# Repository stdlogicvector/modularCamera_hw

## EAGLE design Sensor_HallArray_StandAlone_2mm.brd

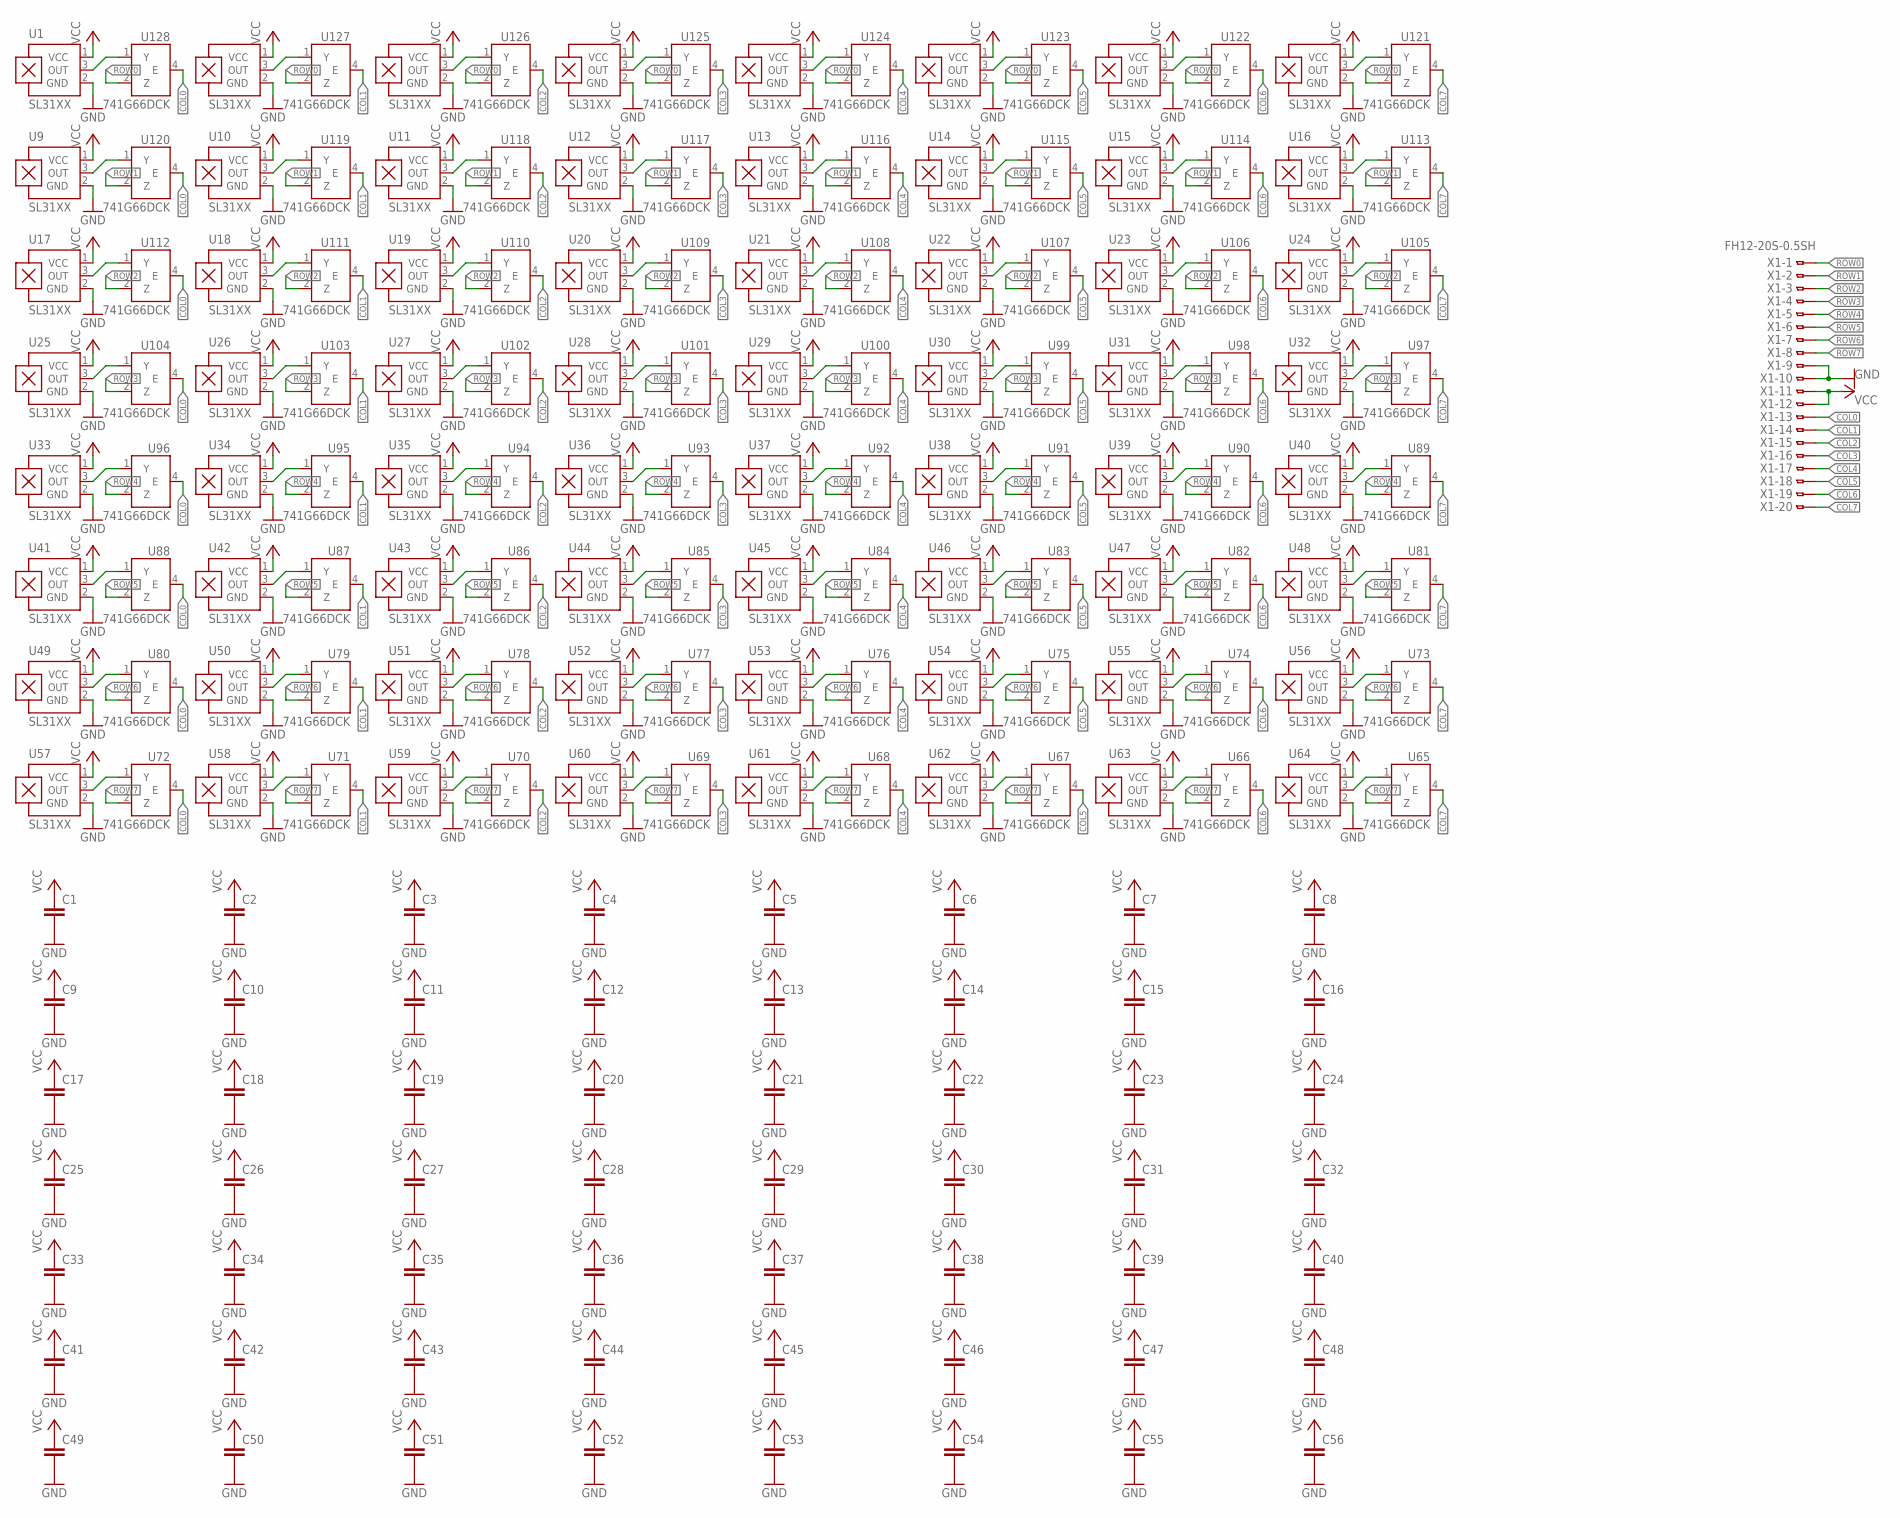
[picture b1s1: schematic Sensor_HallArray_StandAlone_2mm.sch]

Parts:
C1, C2, C3, C4, C5, C6, C7, C8, C9, C10, C11, C12, C13, C14, C15, C16, C17, C18, C19, C20, C21, C22, C23, C24, C25, C26, C27, C28, C29, C30, C31, C32, C33, C34, C35, C36, C37, C38, C39, C40, C41, C42, C43, C44, C45, C46, C47, C48, C49, C50, C51, C52, C53, C54, C55, C56: C-EUC0201; C0201
U1, U2, U3, U4, U5, U6, U7, U8, U9, U10, U11, U12, U13, U14, U15, U16, U17, U18, U19, U20, U21, U22, U23, U24, U25, U26, U27, U28, U29, U30, U31, U32, U33, U34, U35, U36, U37, U38, U39, U40, U41, U42, U43, U44, U45, U46, U47, U48, U49, U50, U51, U52, U53, U54, U55, U56, U57, U58, U59, U60, U61, U62, U63, U64: SL31XX; SOT1215
U65, U66, U67, U68, U69, U70, U71, U72, U73, U74, U75, U76, U77, U78, U79, U80, U81, U82, U83, U84, U85, U86, U87, U88, U89, U90, U91, U92, U93, U94, U95, U96, U97, U98, U99, U100, U101, U102, U103, U104, U105, U106, U107, U108, U109, U110, U111, U112, U113, U114, U115, U116, U117, U118, U119, U120, U121, U122, U123, U124, U125, U126, U127, U128: 741G66DCK; SC70-5
X1: FH12-20S-0.5SH

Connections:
COL0: U72.4 (E), U80.4 (E), U88.4 (E), U96.4 (E), U104.4 (E), U112.4 (E), U120.4 (E), U128.4 (E), X1.13
COL1: U71.4 (E), U79.4 (E), U87.4 (E), U95.4 (E), U103.4 (E), U111.4 (E), U119.4 (E), U127.4 (E), X1.14
COL2: U70.4 (E), U78.4 (E), U86.4 (E), U94.4 (E), U102.4 (E), U110.4 (E), U118.4 (E), U126.4 (E), X1.15
COL3: U69.4 (E), U77.4 (E), U85.4 (E), U93.4 (E), U101.4 (E), U109.4 (E), U117.4 (E), U125.4 (E), X1.16
COL4: U68.4 (E), U76.4 (E), U84.4 (E), U92.4 (E), U100.4 (E), U108.4 (E), U116.4 (E), U124.4 (E), X1.17
COL5: U67.4 (E), U75.4 (E), U83.4 (E), U91.4 (E), U99.4 (E), U107.4 (E), U115.4 (E), U123.4 (E), X1.18
COL6: U66.4 (E), U74.4 (E), U82.4 (E), U90.4 (E), U98.4 (E), U106.4 (E), U114.4 (E), U122.4 (E), X1.19
COL7: U65.4 (E), U73.4 (E), U81.4 (E), U89.4 (E), U97.4 (E), U105.4 (E), U113.4 (E), U121.4 (E), X1.20
GND: C1.2, C2.2, C3.2, C4.2, C5.2, C6.2, C7.2, C8.2, C9.2, C10.2, C11.2, C12.2, C13.2, C14.2, C15.2, C16.2, C17.2, C18.2, C19.2, C20.2, C21.2, C22.2, C23.2, C24.2, C25.2, C26.2, C27.2, C28.2, C29.2, C30.2, C31.2, C32.2, C33.2, C34.2, C35.2, C36.2, C37.2, C38.2, C39.2, C40.2, C41.2, C42.2, C43.2, C44.2, C45.2, C46.2, C47.2, C48.2, C49.2, C50.2, C51.2, C52.2, C53.2, C54.2, C55.2, C56.2, U1.2 (GND), U2.2 (GND), U3.2 (GND), U4.2 (GND), U5.2 (GND), U6.2 (GND), U7.2 (GND), U8.2 (GND), U9.2 (GND), U10.2 (GND), U11.2 (GND), U12.2 (GND), U13.2 (GND), U14.2 (GND), U15.2 (GND), U16.2 (GND), U17.2 (GND), U18.2 (GND), U19.2 (GND), U20.2 (GND), U21.2 (GND), U22.2 (GND), U23.2 (GND), U24.2 (GND), U25.2 (GND), U26.2 (GND), U27.2 (GND), U28.2 (GND), U29.2 (GND), U30.2 (GND), U31.2 (GND), U32.2 (GND), U33.2 (GND), U34.2 (GND), U35.2 (GND), U36.2 (GND), U37.2 (GND), U38.2 (GND), U39.2 (GND), U40.2 (GND), U41.2 (GND), U42.2 (GND), U43.2 (GND), U44.2 (GND), U45.2 (GND), U46.2 (GND), U47.2 (GND), U48.2 (GND), U49.2 (GND), U50.2 (GND), U51.2 (GND), U52.2 (GND), U53.2 (GND), U54.2 (GND), U55.2 (GND), U56.2 (GND), U57.2 (GND), U58.2 (GND), U59.2 (GND), U60.2 (GND), U61.2 (GND), U62.2 (GND), U63.2 (GND), U64.2 (GND), U65.3 (GND), U66.3 (GND), U67.3 (GND), U68.3 (GND), U69.3 (GND), U70.3 (GND), U71.3 (GND), U72.3 (GND), U73.3 (GND), U74.3 (GND), U75.3 (GND), U76.3 (GND), U77.3 (GND), U78.3 (GND), U79.3 (GND), U80.3 (GND), U81.3 (GND), U82.3 (GND), U83.3 (GND), U84.3 (GND), U85.3 (GND), U86.3 (GND), U87.3 (GND), U88.3 (GND), U89.3 (GND), U90.3 (GND), U91.3 (GND), U92.3 (GND), U93.3 (GND), U94.3 (GND), U95.3 (GND), U96.3 (GND), U97.3 (GND), U98.3 (GND), U99.3 (GND), U100.3 (GND), U101.3 (GND), U102.3 (GND), U103.3 (GND), U104.3 (GND), U105.3 (GND), U106.3 (GND), U107.3 (GND), U108.3 (GND), U109.3 (GND), U110.3 (GND), U111.3 (GND), U112.3 (GND), U113.3 (GND), U114.3 (GND), U115.3 (GND), U116.3 (GND), U117.3 (GND), U118.3 (GND), U119.3 (GND), U120.3 (GND), U121.3 (GND), U122.3 (GND), U123.3 (GND), U124.3 (GND), U125.3 (GND), U126.3 (GND), U127.3 (GND), U128.3 (GND), X1.9, X1.10
unnamed: U1.3 (OUT), U128.1 (Y)
unnamed: U2.3 (OUT), U127.1 (Y)
unnamed: U9.3 (OUT), U120.1 (Y)
unnamed: U3.3 (OUT), U126.1 (Y)
unnamed: U4.3 (OUT), U125.1 (Y)
unnamed: U5.3 (OUT), U124.1 (Y)
unnamed: U6.3 (OUT), U123.1 (Y)
unnamed: U7.3 (OUT), U122.1 (Y)
unnamed: U8.3 (OUT), U121.1 (Y)
unnamed: U10.3 (OUT), U119.1 (Y)
unnamed: U11.3 (OUT), U118.1 (Y)
unnamed: U12.3 (OUT), U117.1 (Y)
unnamed: U13.3 (OUT), U116.1 (Y)
unnamed: U14.3 (OUT), U115.1 (Y)
unnamed: U15.3 (OUT), U114.1 (Y)
unnamed: U16.3 (OUT), U113.1 (Y)
unnamed: U17.3 (OUT), U112.1 (Y)
unnamed: U18.3 (OUT), U111.1 (Y)
unnamed: U19.3 (OUT), U110.1 (Y)
unnamed: U20.3 (OUT), U109.1 (Y)
unnamed: U21.3 (OUT), U108.1 (Y)
unnamed: U22.3 (OUT), U107.1 (Y)
unnamed: U23.3 (OUT), U106.1 (Y)
unnamed: U24.3 (OUT), U105.1 (Y)
unnamed: U25.3 (OUT), U104.1 (Y)
unnamed: U26.3 (OUT), U103.1 (Y)
unnamed: U27.3 (OUT), U102.1 (Y)
unnamed: U28.3 (OUT), U101.1 (Y)
unnamed: U29.3 (OUT), U100.1 (Y)
unnamed: U30.3 (OUT), U99.1 (Y)
unnamed: U31.3 (OUT), U98.1 (Y)
unnamed: U32.3 (OUT), U97.1 (Y)
unnamed: U33.3 (OUT), U96.1 (Y)
unnamed: U34.3 (OUT), U95.1 (Y)
unnamed: U35.3 (OUT), U94.1 (Y)
unnamed: U36.3 (OUT), U93.1 (Y)
unnamed: U37.3 (OUT), U92.1 (Y)
unnamed: U38.3 (OUT), U91.1 (Y)
unnamed: U39.3 (OUT), U90.1 (Y)
unnamed: U40.3 (OUT), U89.1 (Y)
unnamed: U41.3 (OUT), U88.1 (Y)
unnamed: U42.3 (OUT), U87.1 (Y)
unnamed: U43.3 (OUT), U86.1 (Y)
unnamed: U44.3 (OUT), U85.1 (Y)
unnamed: U45.3 (OUT), U84.1 (Y)
unnamed: U46.3 (OUT), U83.1 (Y)
unnamed: U47.3 (OUT), U82.1 (Y)
unnamed: U48.3 (OUT), U81.1 (Y)
unnamed: U49.3 (OUT), U80.1 (Y)
unnamed: U50.3 (OUT), U79.1 (Y)
unnamed: U51.3 (OUT), U78.1 (Y)
unnamed: U52.3 (OUT), U77.1 (Y)
unnamed: U53.3 (OUT), U76.1 (Y)
unnamed: U54.3 (OUT), U75.1 (Y)
unnamed: U55.3 (OUT), U74.1 (Y)
unnamed: U56.3 (OUT), U73.1 (Y)
unnamed: U57.3 (OUT), U72.1 (Y)
unnamed: U58.3 (OUT), U71.1 (Y)
unnamed: U59.3 (OUT), U70.1 (Y)
unnamed: U60.3 (OUT), U69.1 (Y)
unnamed: U61.3 (OUT), U68.1 (Y)
unnamed: U62.3 (OUT), U67.1 (Y)
unnamed: U63.3 (OUT), U66.1 (Y)
unnamed: U64.3 (OUT), U65.1 (Y)
ROW0: U121.2 (Z), U122.2 (Z), U123.2 (Z), U124.2 (Z), U125.2 (Z), U126.2 (Z), U127.2 (Z), U128.2 (Z), X1.1
ROW1: U113.2 (Z), U114.2 (Z), U115.2 (Z), U116.2 (Z), U117.2 (Z), U118.2 (Z), U119.2 (Z), U120.2 (Z), X1.2
ROW2: U105.2 (Z), U106.2 (Z), U107.2 (Z), U108.2 (Z), U109.2 (Z), U110.2 (Z), U111.2 (Z), U112.2 (Z), X1.3
ROW3: U97.2 (Z), U98.2 (Z), U99.2 (Z), U100.2 (Z), U101.2 (Z), U102.2 (Z), U103.2 (Z), U104.2 (Z), X1.4
ROW4: U89.2 (Z), U90.2 (Z), U91.2 (Z), U92.2 (Z), U93.2 (Z), U94.2 (Z), U95.2 (Z), U96.2 (Z), X1.5
ROW5: U81.2 (Z), U82.2 (Z), U83.2 (Z), U84.2 (Z), U85.2 (Z), U86.2 (Z), U87.2 (Z), U88.2 (Z), X1.6
ROW6: U73.2 (Z), U74.2 (Z), U75.2 (Z), U76.2 (Z), U77.2 (Z), U78.2 (Z), U79.2 (Z), U80.2 (Z), X1.7
ROW7: U65.2 (Z), U66.2 (Z), U67.2 (Z), U68.2 (Z), U69.2 (Z), U70.2 (Z), U71.2 (Z), U72.2 (Z), X1.8
VCC: C1.1, C2.1, C3.1, C4.1, C5.1, C6.1, C7.1, C8.1, C9.1, C10.1, C11.1, C12.1, C13.1, C14.1, C15.1, C16.1, C17.1, C18.1, C19.1, C20.1, C21.1, C22.1, C23.1, C24.1, C25.1, C26.1, C27.1, C28.1, C29.1, C30.1, C31.1, C32.1, C33.1, C34.1, C35.1, C36.1, C37.1, C38.1, C39.1, C40.1, C41.1, C42.1, C43.1, C44.1, C45.1, C46.1, C47.1, C48.1, C49.1, C50.1, C51.1, C52.1, C53.1, C54.1, C55.1, C56.1, U1.1 (VCC), U2.1 (VCC), U3.1 (VCC), U4.1 (VCC), U5.1 (VCC), U6.1 (VCC), U7.1 (VCC), U8.1 (VCC), U9.1 (VCC), U10.1 (VCC), U11.1 (VCC), U12.1 (VCC), U13.1 (VCC), U14.1 (VCC), U15.1 (VCC), U16.1 (VCC), U17.1 (VCC), U18.1 (VCC), U19.1 (VCC), U20.1 (VCC), U21.1 (VCC), U22.1 (VCC), U23.1 (VCC), U24.1 (VCC), U25.1 (VCC), U26.1 (VCC), U27.1 (VCC), U28.1 (VCC), U29.1 (VCC), U30.1 (VCC), U31.1 (VCC), U32.1 (VCC), U33.1 (VCC), U34.1 (VCC), U35.1 (VCC), U36.1 (VCC), U37.1 (VCC), U38.1 (VCC), U39.1 (VCC), U40.1 (VCC), U41.1 (VCC), U42.1 (VCC), U43.1 (VCC), U44.1 (VCC), U45.1 (VCC), U46.1 (VCC), U47.1 (VCC), U48.1 (VCC), U49.1 (VCC), U50.1 (VCC), U51.1 (VCC), U52.1 (VCC), U53.1 (VCC), U54.1 (VCC), U55.1 (VCC), U56.1 (VCC), U57.1 (VCC), U58.1 (VCC), U59.1 (VCC), U60.1 (VCC), U61.1 (VCC), U62.1 (VCC), U63.1 (VCC), U64.1 (VCC), U65.5 (VCC), U66.5 (VCC), U67.5 (VCC), U68.5 (VCC), U69.5 (VCC), U70.5 (VCC), U71.5 (VCC), U72.5 (VCC), U73.5 (VCC), U74.5 (VCC), U75.5 (VCC), U76.5 (VCC), U77.5 (VCC), U78.5 (VCC), U79.5 (VCC), U80.5 (VCC), U81.5 (VCC), U82.5 (VCC), U83.5 (VCC), U84.5 (VCC), U85.5 (VCC), U86.5 (VCC), U87.5 (VCC), U88.5 (VCC), U89.5 (VCC), U90.5 (VCC), U91.5 (VCC), U92.5 (VCC), U93.5 (VCC), U94.5 (VCC), U95.5 (VCC), U96.5 (VCC), U97.5 (VCC), U98.5 (VCC), U99.5 (VCC), U100.5 (VCC), U101.5 (VCC), U102.5 (VCC), U103.5 (VCC), U104.5 (VCC), U105.5 (VCC), U106.5 (VCC), U107.5 (VCC), U108.5 (VCC), U109.5 (VCC), U110.5 (VCC), U111.5 (VCC), U112.5 (VCC), U113.5 (VCC), U114.5 (VCC), U115.5 (VCC), U116.5 (VCC), U117.5 (VCC), U118.5 (VCC), U119.5 (VCC), U120.5 (VCC), U121.5 (VCC), U122.5 (VCC), U123.5 (VCC), U124.5 (VCC), U125.5 (VCC), U126.5 (VCC), U127.5 (VCC), U128.5 (VCC), X1.11, X1.12

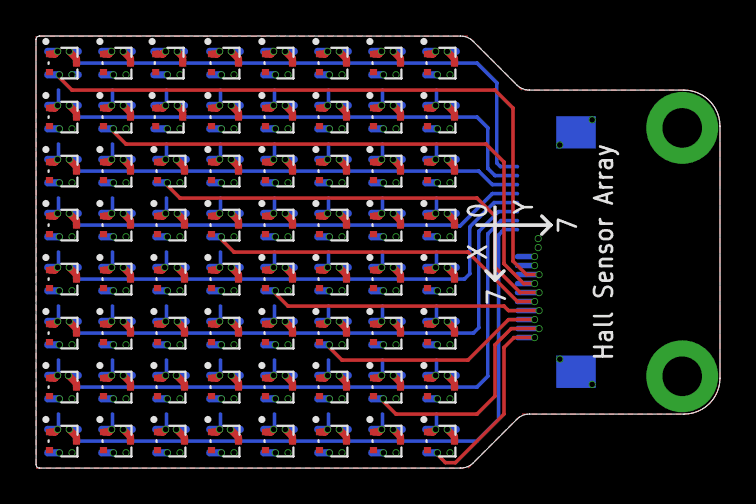
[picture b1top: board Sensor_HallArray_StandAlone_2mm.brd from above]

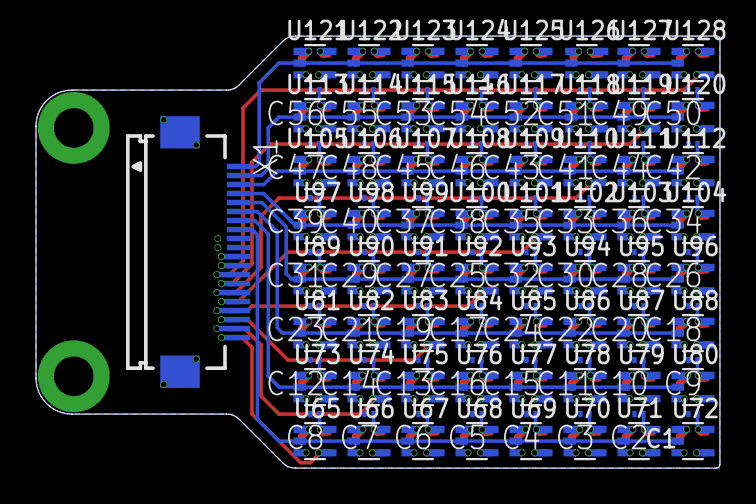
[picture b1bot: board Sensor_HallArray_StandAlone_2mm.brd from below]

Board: 4 copper layers, 38.0 x 24.0 mm, 185 parts (121 on the bottom side), 82 nets.

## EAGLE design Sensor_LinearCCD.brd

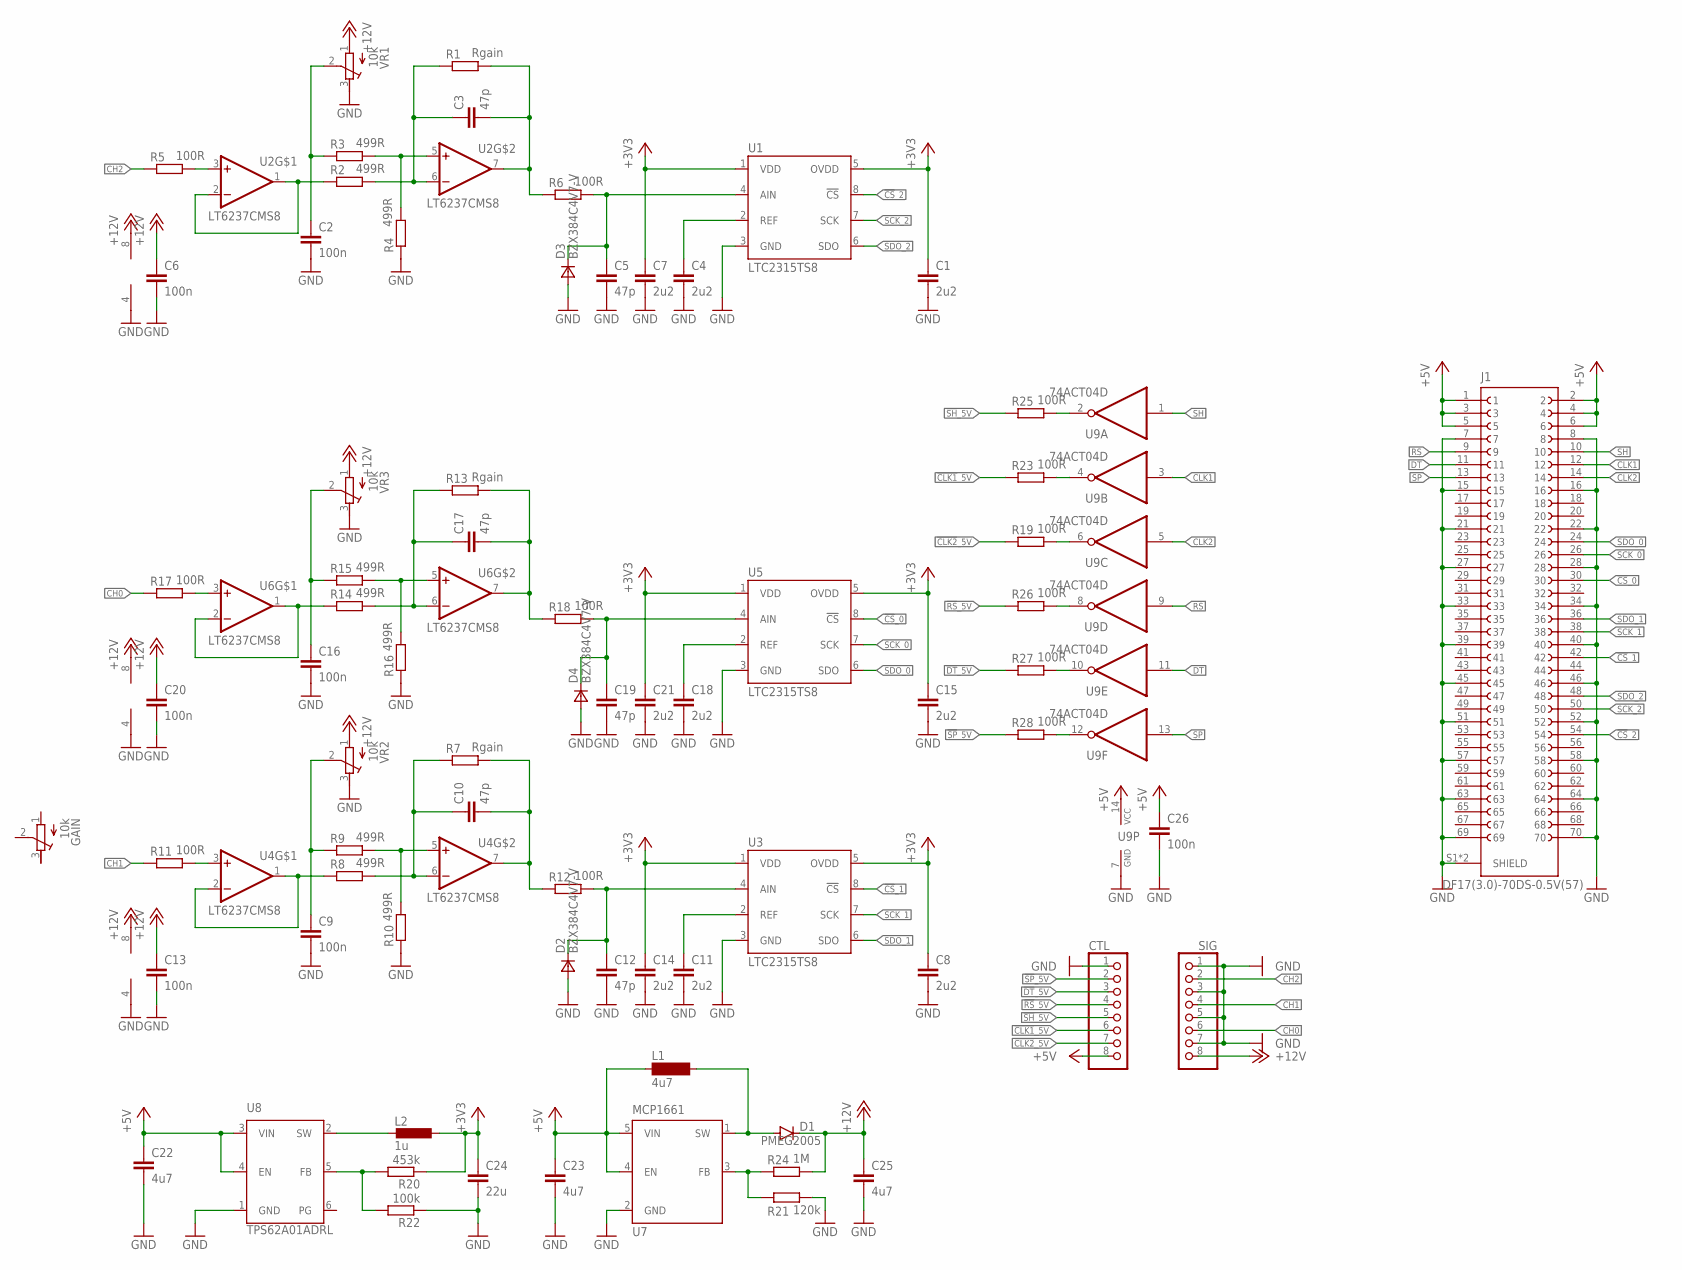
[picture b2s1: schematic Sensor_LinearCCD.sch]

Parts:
C1, C4, C7, C8, C11, C14, C15, C18, C21: 2u2; C0603; LCSC C19666
C2, C6, C9, C13, C16, C20, C26: 100n; C0402
C3, C5, C10, C12, C17, C19: 47p; C0402
C22, C23, C25: 4u7; C0603; LCSC C19666
C24: 22u; C0603; LCSC C109448
CTL: PINHD-1X8_2.00; 1X08M
D1: PMEG2005; SOD123; DIGIKEY 1727-7330-1-ND
D2, D3, D4: BZX384C4V7-V; SOD323
GAIN: 10k; RTRIM3224J
J1: DF17(3.0)-70DS-0.5V(57)
L1: 4u7; L4012
L2: 1u; L1008; MPN LQM2HPN1R0MG0L; DIGIKEY 490-5112-1-ND
R1, R7, R13: Rgain; R0402
R2, R3, R4, R8, R9, R10, R14, R15, R16: 499R; R0402
R5, R6, R11, R12, R17, R18, R19, R23, R25, R26, R27, R28: 100R; R0402
R20: 453k; R0402; LCSC C137978
R21: 120k; R0402
R22: 100k; R0402; DIGIKEY RMCF0402FT100KCT-ND
R24: 1M; R0402
SIG: PINHD-1X8_2.00; 1X08M
U1, U3, U5: LTC2315TS8; SOT23-8L
U2, U4, U6: LT6237CMS8; MSOP08
U7: MCP1661; SOT23-5L; DIGIKEY MCP1661T-E/OTCT-ND
U8: TPS62A01ADRL; SOTFL50P160X60-6N; DIGIKEY 296-TPS62A01ADRLRCT-ND
U9: 74ACT04D; SO14
VR1, VR2, VR3: 10k; RTRIM3224J

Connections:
!CLK1!_5V: CTL.6, R23.1
!CLK2!_5V: CTL.7, R19.1
!CS!_0: J1.30, U5.8 (!CS)
!CS!_1: J1.42, U3.8 (!CS)
!CS!_2: J1.54, U1.8 (!CS)
!DT!_5V: CTL.3, R27.1
!RS!_5V: CTL.4, R26.1
!SH!_5V: CTL.5, R25.1
!SP!_5V: CTL.2, R28.1
+3V3: C1.1, C7.1, C8.1, C14.1, C15.1, C21.1, C24.1, L2.1, R20.1, U1.1 (VDD), U1.5 (OVDD), U3.1 (VDD), U3.5 (OVDD), U5.1 (VDD), U5.5 (OVDD)
+5V: C22.1, C23.1, C26.1, CTL.8, J1.1, J1.2, J1.3, J1.4, J1.5, J1.6, L1.1, U7.4 (EN), U7.5 (VIN), U8.3 (VIN), U8.4 (EN), U9.14 (VCC)
+12V: C6.1, C13.1, C20.1, C25.1, D1.C, R24.2, SIG.8, U2.8 (V+), U4.8 (V+), U6.8 (V+), VR1.1 (A), VR2.1 (A), VR3.1 (A)
CH0: R17.1, SIG.6
CH1: R11.1, SIG.4
CH2: R5.1, SIG.2
CLK1: J1.12, U9.3 (I)
CLK2: J1.14, U9.5 (I)
DT: J1.11, U9.11 (I)
GND: C1.2, C2.2, C4.2, C5.2, C6.2, C7.2, C8.2, C9.2, C11.2, C12.2, C13.2, C14.2, C15.2, C16.2, C18.2, C19.2, C20.2, C21.2, C22.2, C23.2, C24.2, C25.2, C26.2, CTL.1, D2.2 (A), D3.2 (A), D4.2 (A), J1.7, J1.8, J1.15, J1.16, J1.21, J1.22, J1.27, J1.28, J1.33, J1.34, J1.39, J1.40, J1.45, J1.46, J1.51, J1.52, J1.57, J1.58, J1.63, J1.64, J1.69, J1.70, J1.S1 (SHIELD), J1.S2 (SHIELD), R4.1, R10.1, R16.1, R21.2, R22.1, SIG.1, SIG.3, SIG.5, SIG.7, U1.3 (GND), U2.4 (V-), U3.3 (GND), U4.4 (V-), U5.3 (GND), U6.4 (V-), U7.2 (GND), U8.1 (GND), U9.7 (GND), VR1.3 (E), VR2.3 (E), VR3.3 (E)
unnamed: R21.1, R24.1, U7.3 (FB)
unnamed: C11.1, U3.2 (REF)
unnamed: D1.A, L1.2, U7.1 (SW)
unnamed: C12.1, D2.1 (C), R12.2, U3.4 (AIN)
unnamed: R8.1, U4.1 (OUT), U4.2 (-IN)
unnamed: R11.2, U4.3 (+IN)
unnamed: C10.1, R7.1, R8.2, U4.6 (-IN)
unnamed: C10.2, R7.2, R12.1, U4.7 (OUT)
unnamed: R25.2, U9.2 (O)
unnamed: R23.2, U9.4 (O)
unnamed: R19.2, U9.6 (O)
unnamed: R26.2, U9.8 (O)
unnamed: R27.2, U9.10 (O)
unnamed: R28.2, U9.12 (O)
unnamed: C9.1, R9.1, VR2.2 (S)
unnamed: R9.2, R10.2, U4.5 (+IN)
unnamed: C18.1, U5.2 (REF)
unnamed: C19.1, D4.1 (C), R18.2, U5.4 (AIN)
unnamed: R14.1, U6.1 (OUT), U6.2 (-IN)
unnamed: R17.2, U6.3 (+IN)
unnamed: C17.1, R13.1, R14.2, U6.6 (-IN)
unnamed: C17.2, R13.2, R18.1, U6.7 (OUT)
unnamed: C16.1, R15.1, VR3.2 (S)
unnamed: R15.2, R16.2, U6.5 (+IN)
unnamed: C4.1, U1.2 (REF)
unnamed: C5.1, D3.1 (C), R6.2, U1.4 (AIN)
unnamed: R2.1, U2.1 (OUT), U2.2 (-IN)
unnamed: R5.2, U2.3 (+IN)
unnamed: C3.1, R1.1, R2.2, U2.6 (-IN)
unnamed: C3.2, R1.2, R6.1, U2.7 (OUT)
unnamed: C2.1, R3.1, VR1.2 (S)
unnamed: R3.2, R4.2, U2.5 (+IN)
unnamed: R20.2, R22.2, U8.5 (FB)
unnamed: L2.2, U8.2 (SW)
RS: J1.9, U9.9 (I)
SCK_0: J1.26, U5.7 (SCK)
SCK_1: J1.38, U3.7 (SCK)
SCK_2: J1.50, U1.7 (SCK)
SDO_0: J1.24, U5.6 (SDO)
SDO_1: J1.36, U3.6 (SDO)
SDO_2: J1.48, U1.6 (SDO)
SH: J1.10, U9.1 (I)
SP: J1.13, U9.13 (I)

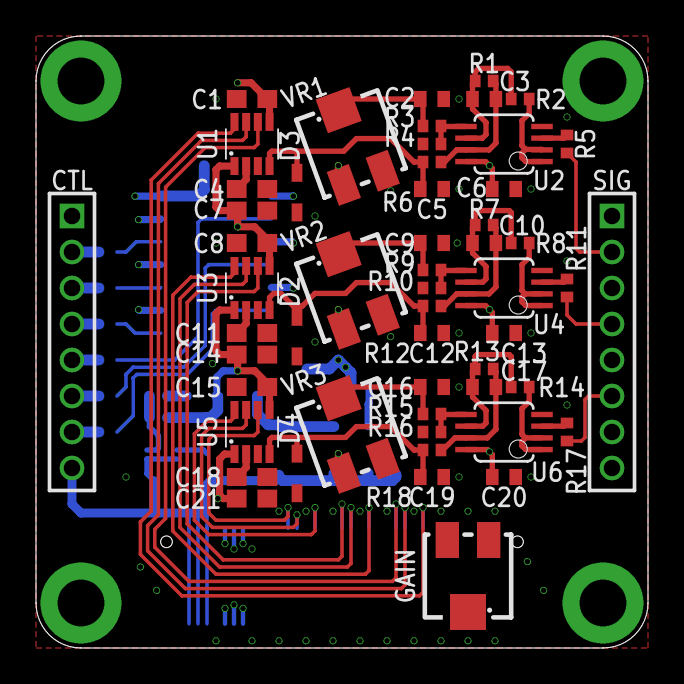
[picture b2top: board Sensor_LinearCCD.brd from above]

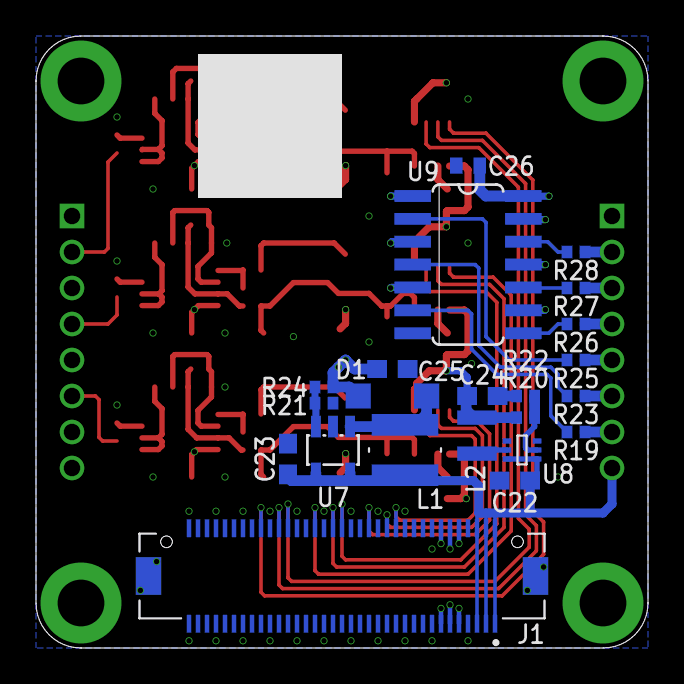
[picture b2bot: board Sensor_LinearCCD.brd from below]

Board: 4 copper layers, 34.0 x 34.0 mm, 76 parts (22 on the bottom side), 62 nets.

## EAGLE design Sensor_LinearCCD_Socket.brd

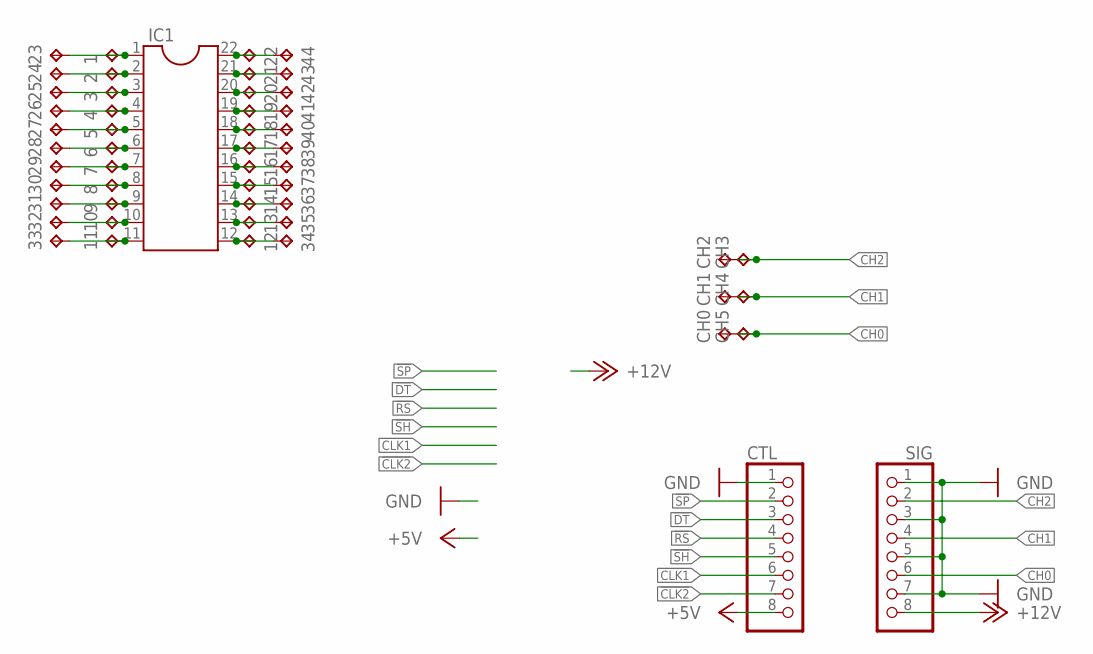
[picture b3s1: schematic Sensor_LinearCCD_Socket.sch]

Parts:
1, 2, 3, 4, 5, 6, 7, 8, 9, 10, 11, 12, 13, 14, 15, 16, 17, 18, 19, 20, 21, 22, 23, 24, 25, 26, 27, 28, 29, 30, 31, 32, 33, 34, 35, 36, 37, 38, 39, 40, 41, 42, 43, 44: TPTP15SQ; TP15SQ
CH0, CH1, CH2, CH3, CH4, CH5: TPTP15SQ; TP15SQ
CTL: PINHD-1X8_2.00; 1X08M
IC1: DIL22-4
SIG: PINHD-1X8_2.00; 1X08M

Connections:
!CLK1!: CTL.6
!CLK2!: CTL.7
!DT!: CTL.3
!RS!: CTL.4
!SH!: CTL.5
!SP!: CTL.2
+5V: CTL.8
+12V: SIG.8
CH0: CH0.TP, CH5.TP, SIG.6
CH1: CH1.TP, CH4.TP, SIG.4
CH2: CH2.TP, CH3.TP, SIG.2
GND: CTL.1, SIG.1, SIG.3, SIG.5, SIG.7
unnamed: 1.TP, 23.TP, IC1.1
unnamed: 2.TP, 24.TP, IC1.2
unnamed: 3.TP, 25.TP, IC1.3
unnamed: 4.TP, 26.TP, IC1.4
unnamed: 5.TP, 27.TP, IC1.5
unnamed: 6.TP, 28.TP, IC1.6
unnamed: 7.TP, 29.TP, IC1.7
unnamed: 8.TP, 30.TP, IC1.8
unnamed: 9.TP, 31.TP, IC1.9
unnamed: 10.TP, 32.TP, IC1.10
unnamed: 11.TP, 33.TP, IC1.11
unnamed: 12.TP, 34.TP, IC1.12
unnamed: 13.TP, 35.TP, IC1.13
unnamed: 14.TP, 36.TP, IC1.14
unnamed: 15.TP, 37.TP, IC1.15
unnamed: 16.TP, 38.TP, IC1.16
unnamed: 17.TP, 39.TP, IC1.17
unnamed: 18.TP, 40.TP, IC1.18
unnamed: 19.TP, 41.TP, IC1.19
unnamed: 20.TP, 42.TP, IC1.20
unnamed: 21.TP, 43.TP, IC1.21
unnamed: 22.TP, 44.TP, IC1.22

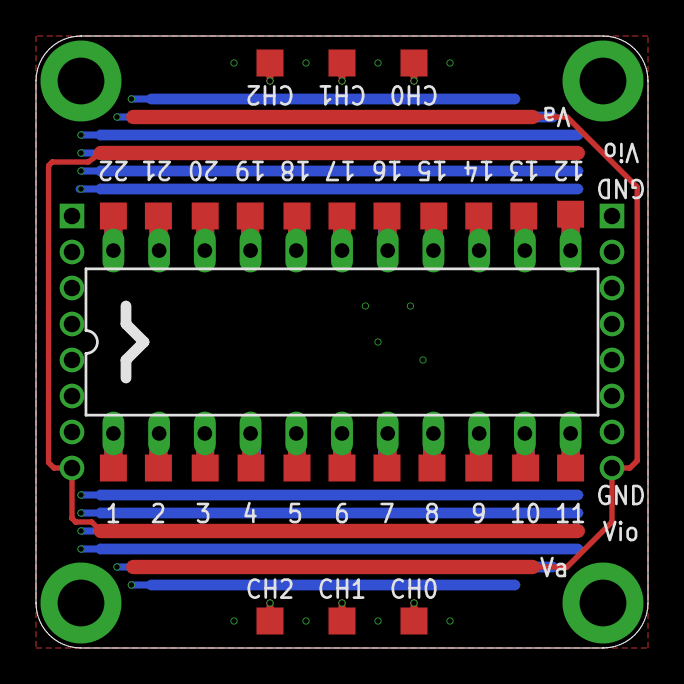
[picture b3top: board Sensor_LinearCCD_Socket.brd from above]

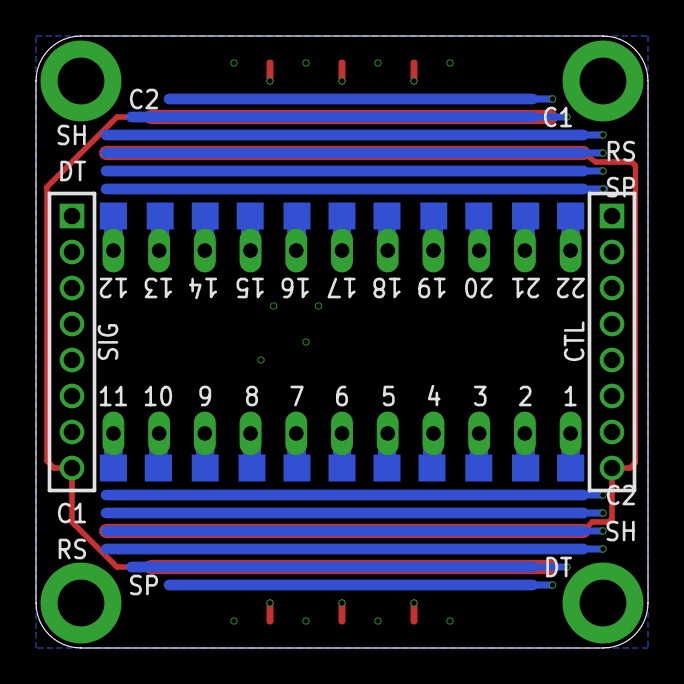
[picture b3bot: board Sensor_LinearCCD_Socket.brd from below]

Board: 4 copper layers, 34.0 x 34.0 mm, 53 parts (24 on the bottom side), 26 nets.

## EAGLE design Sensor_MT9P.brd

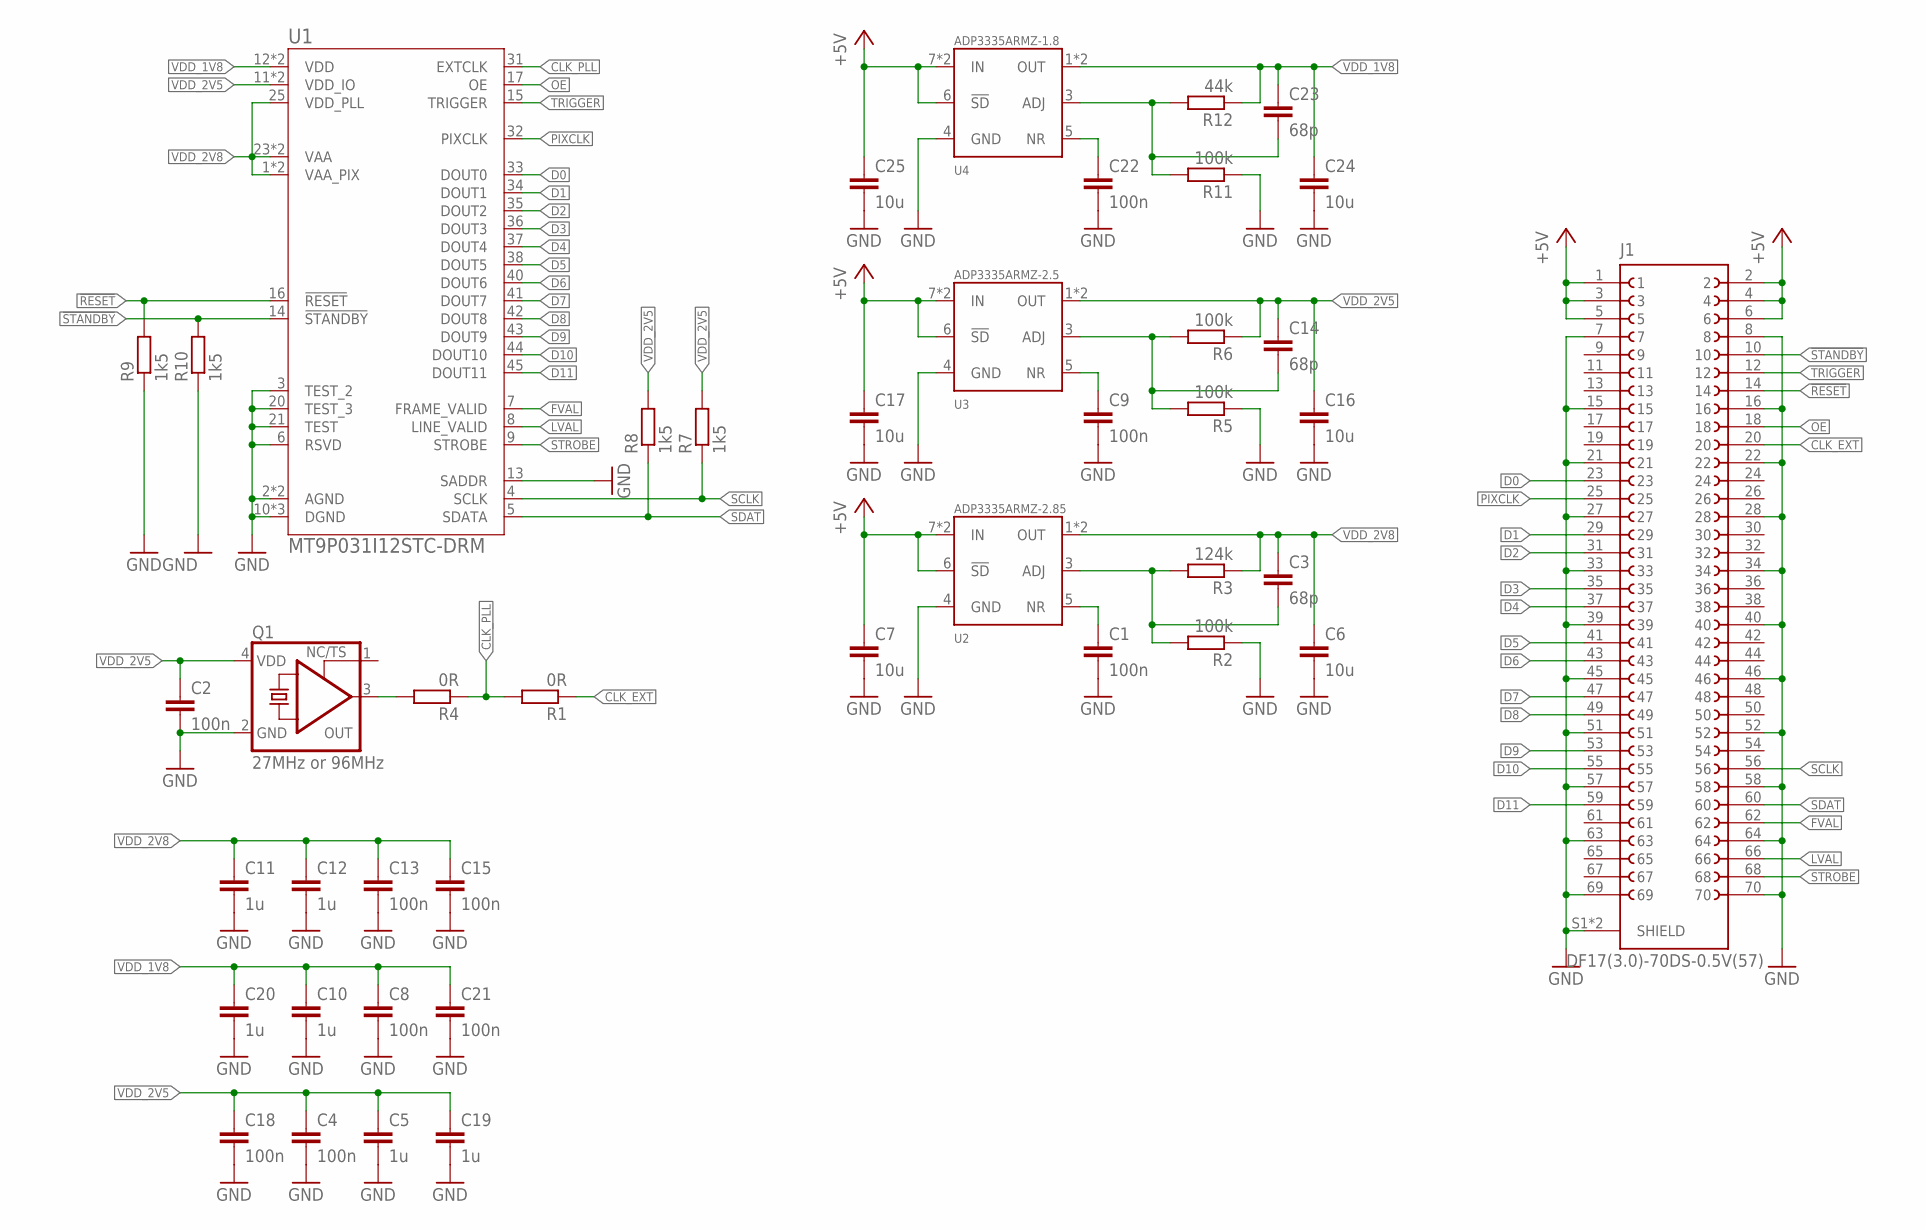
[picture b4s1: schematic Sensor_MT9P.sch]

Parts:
C1, C2, C4, C8, C9, C13, C15, C18, C21, C22: 100n; C0402; LCSC C1525
C3, C14, C23: 68p; C0402; LCSC C1525
C5, C10, C11, C12, C19, C20: 1u; C0402
C6, C7, C16, C17, C24, C25: 10u; C0603
J1: DF17(3.0)-70DS-0.5V(57)
Q1: 27MHz or 96MHz; 3.2X2.5_KXO-V96
R1, R4: 0R; R0402
R2, R5, R6, R11: 100k; R0402
R3: 124k; R0402
R7, R8, R9, R10: 1k5; R0402
R12: 44k; R0402
U1: MT9P031I12STC-DRM; ILCC48_10X10_847AA-O_OSI-M
U2: ADP3335ARMZ-2.85; MSOP08; DIGIKEY 505-ADP3335ARMZ-3.3RL7CT-ND
U3: ADP3335ARMZ-2.5; MSOP08; DIGIKEY 505-ADP3335ARMZ-2.5-RLCT-ND
U4: ADP3335ARMZ-1.8; MSOP08; DIGIKEY 505-ADP3335ARMZ-1.8-R7CT-ND

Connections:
!RESET: J1.14, R9.2, U1.16 (!RESET)
!STANDBY: J1.10, R10.2, U1.14 (!STANDBY)
+5V: C7.1, C17.1, C25.1, J1.1, J1.2, J1.3, J1.4, J1.5, J1.6, U2.6 (!SD), U2.7 (IN), U2.8 (IN), U3.6 (!SD), U3.7 (IN), U3.8 (IN), U4.6 (!SD), U4.7 (IN), U4.8 (IN)
CLK: Q1.3 (OUT), R4.2
CLK_EXT: J1.20, R1.1
CLK_PLL: R1.2, R4.1, U1.31 (EXTCLK)
D0: J1.23, U1.33 (DOUT0)
D1: J1.29, U1.34 (DOUT1)
D2: J1.31, U1.35 (DOUT2)
D3: J1.35, U1.36 (DOUT3)
D4: J1.37, U1.37 (DOUT4)
D5: J1.41, U1.38 (DOUT5)
D6: J1.43, U1.40 (DOUT6)
D7: J1.47, U1.41 (DOUT7)
D8: J1.49, U1.42 (DOUT8)
D9: J1.53, U1.43 (DOUT9)
D10: J1.55, U1.44 (DOUT10)
D11: J1.59, U1.45 (DOUT11)
FVAL: J1.62, U1.7 (FRAME_VALID)
GND: C1.2, C2.2, C4.2, C5.2, C6.2, C7.2, C8.2, C9.2, C10.2, C11.2, C12.2, C13.2, C15.2, C16.2, C17.2, C18.2, C19.2, C20.2, C21.2, C22.2, C24.2, C25.2, J1.7, J1.8, J1.15, J1.16, J1.21, J1.22, J1.27, J1.28, J1.33, J1.34, J1.39, J1.40, J1.45, J1.46, J1.51, J1.52, J1.57, J1.58, J1.63, J1.64, J1.69, J1.70, J1.S1 (SHIELD), J1.S2 (SHIELD), Q1.2 (GND), R2.1, R5.1, R9.1, R10.1, R11.1, U1.2 (AGND), U1.3 (TEST_2), U1.6 (RSVD), U1.10 (DGND), U1.13 (SADDR), U1.20 (TEST_3), U1.21 (TEST), U1.22 (AGND), U1.26 (DGND), U1.46 (DGND), U2.4 (GND), U3.4 (GND), U4.4 (GND)
LVAL: J1.66, U1.8 (LINE_VALID)
unnamed: C1.1, U2.5 (NR)
unnamed: C22.1, U4.5 (NR)
unnamed: C9.1, U3.5 (NR)
unnamed: C23.2, R11.2, R12.2, U4.3 (ADJ)
unnamed: C14.2, R5.2, R6.2, U3.3 (ADJ)
unnamed: C3.2, R2.2, R3.2, U2.3 (ADJ)
OE: J1.18, U1.17 (OE)
PIXCLK: J1.25, U1.32 (PIXCLK)
SCLK: J1.56, R7.1, U1.4 (SCLK)
SDAT: J1.60, R8.1, U1.5 (SDATA)
STROBE: J1.68, U1.9 (STROBE)
TRIGGER: J1.12, U1.15 (TRIGGER)
VDD_1V8: C8.1, C10.1, C20.1, C21.1, C23.1, C24.1, R12.1, U1.12 (VDD), U1.47 (VDD), U4.1 (OUT), U4.2 (OUT)
VDD_2V5: C2.1, C4.1, C5.1, C14.1, C16.1, C18.1, C19.1, Q1.4 (VDD), R6.1, R7.2, R8.2, U1.11 (VDD_IO), U1.39 (VDD_IO), U3.1 (OUT), U3.2 (OUT)
VDD_2V8: C3.1, C6.1, C11.1, C12.1, C13.1, C15.1, R3.1, U1.1 (VAA_PIX), U1.23 (VAA), U1.24 (VAA), U1.25 (VDD_PLL), U1.48 (VAA_PIX), U2.1 (OUT), U2.2 (OUT)

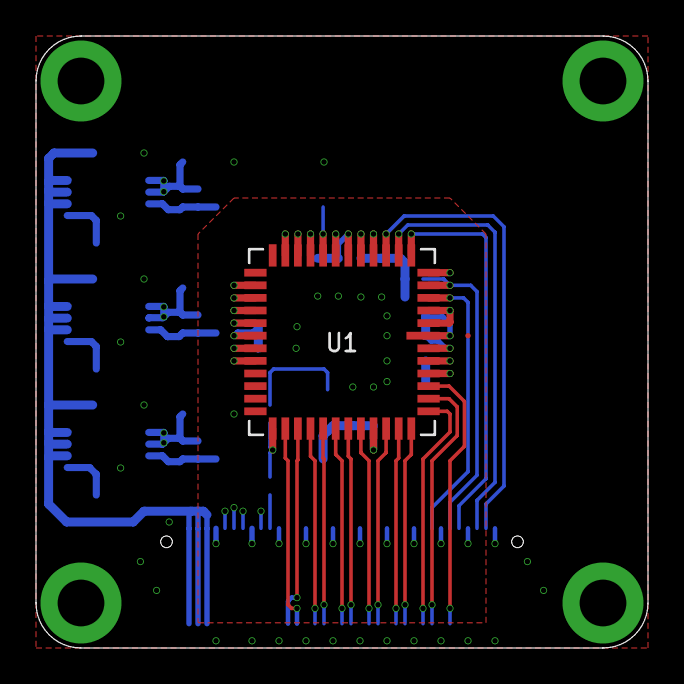
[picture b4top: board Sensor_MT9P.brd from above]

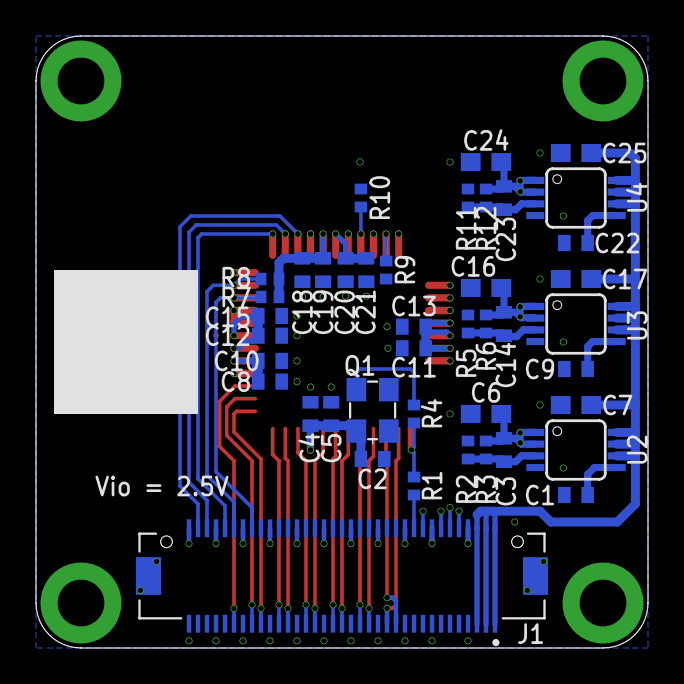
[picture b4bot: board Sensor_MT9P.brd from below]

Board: 4 copper layers, 34.0 x 34.0 mm, 43 parts (42 on the bottom side), 36 nets.

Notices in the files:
parts and their libraries:
crystal-geyer_V1_0: Copyright: Geyer-Electronic
